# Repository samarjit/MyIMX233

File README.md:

# Let me see if I can build a linux Computer (It works now!)

I am starting to build a single board computer with freescale microprocessor iMX233 128 LQFP and 64MB DDR2 SDRAM in 66TSOP. This single board computer will be bare bones with lots of GPIO exposed.
There is no special goal for this project. I am just curious to see if it works. In future I might add an LCD. The PCB is two layered only and can be manufactured cheap.

## TODOs (done)
* Increase pad lengths of LQFP footprint. (done. Hope to mitigate the soldermask between pads issue  |<-0.06mm space-><-0.08mm web-><-0.06mm space->|  = 0.2mm) 
* Perhaps add a jumper on the 2.5v LineReg and separate out VDD_MEM to be able to test the 2.5v is not 0 due to loading. (skipped)
* 88 USB_ID SSP1_DETECT ? Should I use this to CD of SD card connector or micro USB ID pin?  In my circuit it is pulled low via LED. Tux,calculator does the same too.
* Add option to boot resistors LCD_RS and LCD_00..LCD_05 (done)
* 14 LCD_RS ? High for register boot mode. Or low with 47k resistor for OTP boot mode. Olimex is confusing OTP is set MMBR and LCD_RS is high. (done)
* Schottkey Diode D1 VDD4P2 direction. Its strange in ref diagram vs 5v wall. VDD4P2 -|>||- VDDBATT. (done Optional. Not populated in running board)
* Series resistor 1E for preventing oscillations (done 3 series resistor added, usb, batt, 4p2)
/in old circuit Test by removing Diode, and LED_RS to gnd via resistor.
* RESET circuit? Make sure not to get into USB recovery mode. add zener 1.0v so that it never reached 3.3v or just remove reset circuit altogether.
* Configure to get rid of batteries as per rev-c circuit. Add 1k resistors in DCDC_BATT and BATT and some caps to GND.
* Need to convert the SD card connector to a cheaper version available on ebay or alibaba. (done part-ATTEND 112J-TDAR-R01)
I got the files from https://forum.kicad.info/t/microsd-component-footprint-help/3095/5 and placed in parts/ folder. 
It would be awesome if I can find some 3D model of it. If someone finds it please create an issue. (Yes found)
* Make DDR RAM pin pads longer (new)
* Make alternate USB plug preferably through hole or longer pads in micro USB. (new)
* Make micro-SD pads larger and longer and add a few decoupling capacitors.(new)
* Make more rooms for the inductor as most inductors are really big 8mm long plus place for hand soldering.(new)

## TODOs (ignored)
* POWER off circuit? 
* Is Micro SD pullups on all pins necessary? SSP1_DETECT used? (done added them in the bottom side. Data3/CS pulled low)
* Added 120R between CLK nCLK.

### Length Tuning
* D0..D7 LDQS LDM - 39.7mm tuning (real 40.2mm)
* CLK nCLK - real 32.2/32.6mm
* D8..D15 UDQS UDM - 25.5mm tuning (real 26.0mm)
* Address: 32.35mm ~ 25mm
* CKE- 20.2mm
* SD: 24.8mm tuning (real 25.3mm)

## Installation steps
Cloning this repository should work.
It does use opendous
conn_fci from https://github.com/cpavlina/kicad-pcblib.git, https://github.com/cpavlina/kicad-schlib.git
Copy kicad-pcblib\conn-fci.pretty to  KiCad\share\kicad\modules\conn-fci.pretty
Add kicad-schlib-master\library\conn-fci.lib  to SchematicEditor -> ComponentLibraries
Add opendous to component libraries too.

## Drivers for this project.
* Until recently I didn't know of a decent opensource software for PCB designing or circuit designing which can be used to design complicated circuits involving microprocessor.
I recently discovered KiCAD which is opensource pcb designing software and people have done microprocessor design with it eg. OLinuXino. I am trying to learn PCB designing using KiCAD now.
* Second driver was Clementine Core project which I saw in circuitmaker website. This schematic looked so simple and pcb was on 2 layer design, which changed my thought process altogether that linux running board designs may be something I can try.
* Third driver was LibreCalc which almost proved that KiCAD can be used to design IMX233 based board. I hope to learn from their mistakes, but a newbee like me can uncover a whole lot of new mystries.

So I have put together a mashup of schematic design of IMX233 and 64MB RAM from freescale reference design and other sources. 

**Freescale microprocessor:**
* MCIMX233CAG4C

**DDR RAM - I think all these below RAM chips are compatible.**
* AS4C32M16MD1-5TCN
* HY5DU121622D(L)T(P)-J
* MT46V32M16P-5B:J (This is the only one I can source, so I am using this)

This project is a work in progress and there is no gurantee that I will ever be able to complete it :).

But if you want to try building same stuff as I am building. Go ahead and fork it.
Download KiCad. I am using nightly version of it, because it does not require you to export the netlist and import it again in pcb editor. Make the workflow really easy.
I can see one bug in KiCAD, which is after modifying the footprint by adding a step file. It looses the saved settings. 

Once you have installed KiCAD, open **MyIMX233.pro** file. 

[MyIMX233.sch](MyIMX233.sch) - Schematic file.

[MyIMX233.kicad_pcb](MyIMX233.kicad_pcb) - PCB

[ReferenceSch](ReferenceSch) - contains reference materials. I uploaded all of them for providing content incase someone wants to understand the design.

## Progress: 

### Oct 8 It worked! You can start building one today for yourself :)
Few soldering quirks are there. USB pads are quite small to solder. Also pad to hold USB in place is also very small and bad for soldering. Even the SD card pads are also small for soldering. These were new footprints so in next version I will make longer pads for these. RAM pads can be made slightly longer for reliable soldering. 
Soldered board and powered up without SD card. Some error were coming 0x80207002. Boot loader looking for I2C and it is not initialized. Turned out to be soldering of one pin was not proper for LQFP128. Fixed this pin issue then SD card missing related errors were coming. Added SD card with bogus data 0x8020A007 - ERROR_DDI_SD_CONFIG_BLOCK_NOT_FOUND. Added SD card formatted properly but still 0x8020A007. Little bit further digging showed that SD card MBR boot is not enabled by default. We need to burn an OPT bit HW_OCOTP_ROM0::SD_MBR_BOOT to enable booting from SD card. This process is irreversible. Default boot mode is BCB. I read up again librecalc's failure blog.  It gave two perl programs to burn the SD card with u-boot in BCB mode. The 2nd perl program didn't run as it assumed smaller SD cards only. I edited the perl program to make it find proper boot signatures. Now we can see something HTLC in UART console.
That's too less info to debug further. At this point I posted in freescale community. https://community.nxp.com/message/949934. I decided to blow the MBR OTP flag using BitBurner. Then added MBR based uSD card and same u-boot. Now again it shows HTLC. Good news is that MBR booting works. But it fails very soon. Need bootlets which gives more detailed log instead of u-boot. Turned out voltages are fluctuating all 3v3, 4v2, 1v8, 1v. They were fluctuating in a cycle. I burned official Olinuxino image in SD card. That seems to have bootlets so it gave more info. After right after memory `FRAC 0x92926192` it reboots. I heated up all the pins of DDR and iMX233 with soldering iron. It goes 1 more line ahead in log `init_ddr_mt46v32m16_133Mhz` and sometimes `power 0x00820710`. I added a big capacitor in place of battery which goes the log to further and says uSD card general error ending with r14<0>HTLLLL... I tried adding a few caps on 3v3. But nothing helped. Then I tried the other jumper of battery mode. Then it started loading kernel. 

### Aug 2017
Started modifying the schematic to make battery and USB wall power optional using jumpers. Also realized boot selection can be done using resistors. Sent for fabrication of PCB to pcbpower.

### July 2017 end first soldered board
Good news is most of the components fitted. Also I got some confidence about my KiCAD skills.
Some shortcomings were observed, like the pads for soldering were two short for the fine pitched LQFP128 0.4mm pitch and solder mask dams were not created between pads which made it incredibly hard to solder. I will have to customize the LQFP128 footprint to make it suitable for hand soldering. Some 0402 caps were placed very close, I realized the courtyard verification of components is not turned on by default. I had limited success like UART was working USB was working, BitBurner was working and showing all the OPT(One Time Programmable) bits. Some gibberish was coming on UART console. I used solder paste for soldering, so I thought some shorting might be happening. Then I tried to do reflow soldering to make the solder joints liquify once and then quickly cool it using a frying pan. It actually fried my board! I also mistakenly soldered uSD card with power on! Carelessness!

* I also ordered components. I didn't realize this would be a pain. element14 is not that accessible for an individual. I ordered mostly from Shelfkey and some from KitsNSpares. I am still tensed if footprints I chose will match the actual components. Second I am very much tensed about soldering 0402 components.
* Final version of PCB sent for fab in pcbpower. 

* Added few options to use DCDC. I was not comfortable of grounding DCDC_BATT and BATT pins, so I added a few jumpers. Also added provisions to add battery. 

* Learnt basic Freecad to build the Step files of DDR SDRAM 66TSOP. Here is the project I created - [MT46V32M16P-5B-Freecad-Step](https://github.com/samarjit/MT46V32M16P-5B-Freecad-Step).

* Initial version. DDR RAM child 3D missing and SD card's 3D missing.

* Learnt Length Matching in Kicad. 

* Figured out placement of components. I am going with Clementine Core's placement which seems very good.

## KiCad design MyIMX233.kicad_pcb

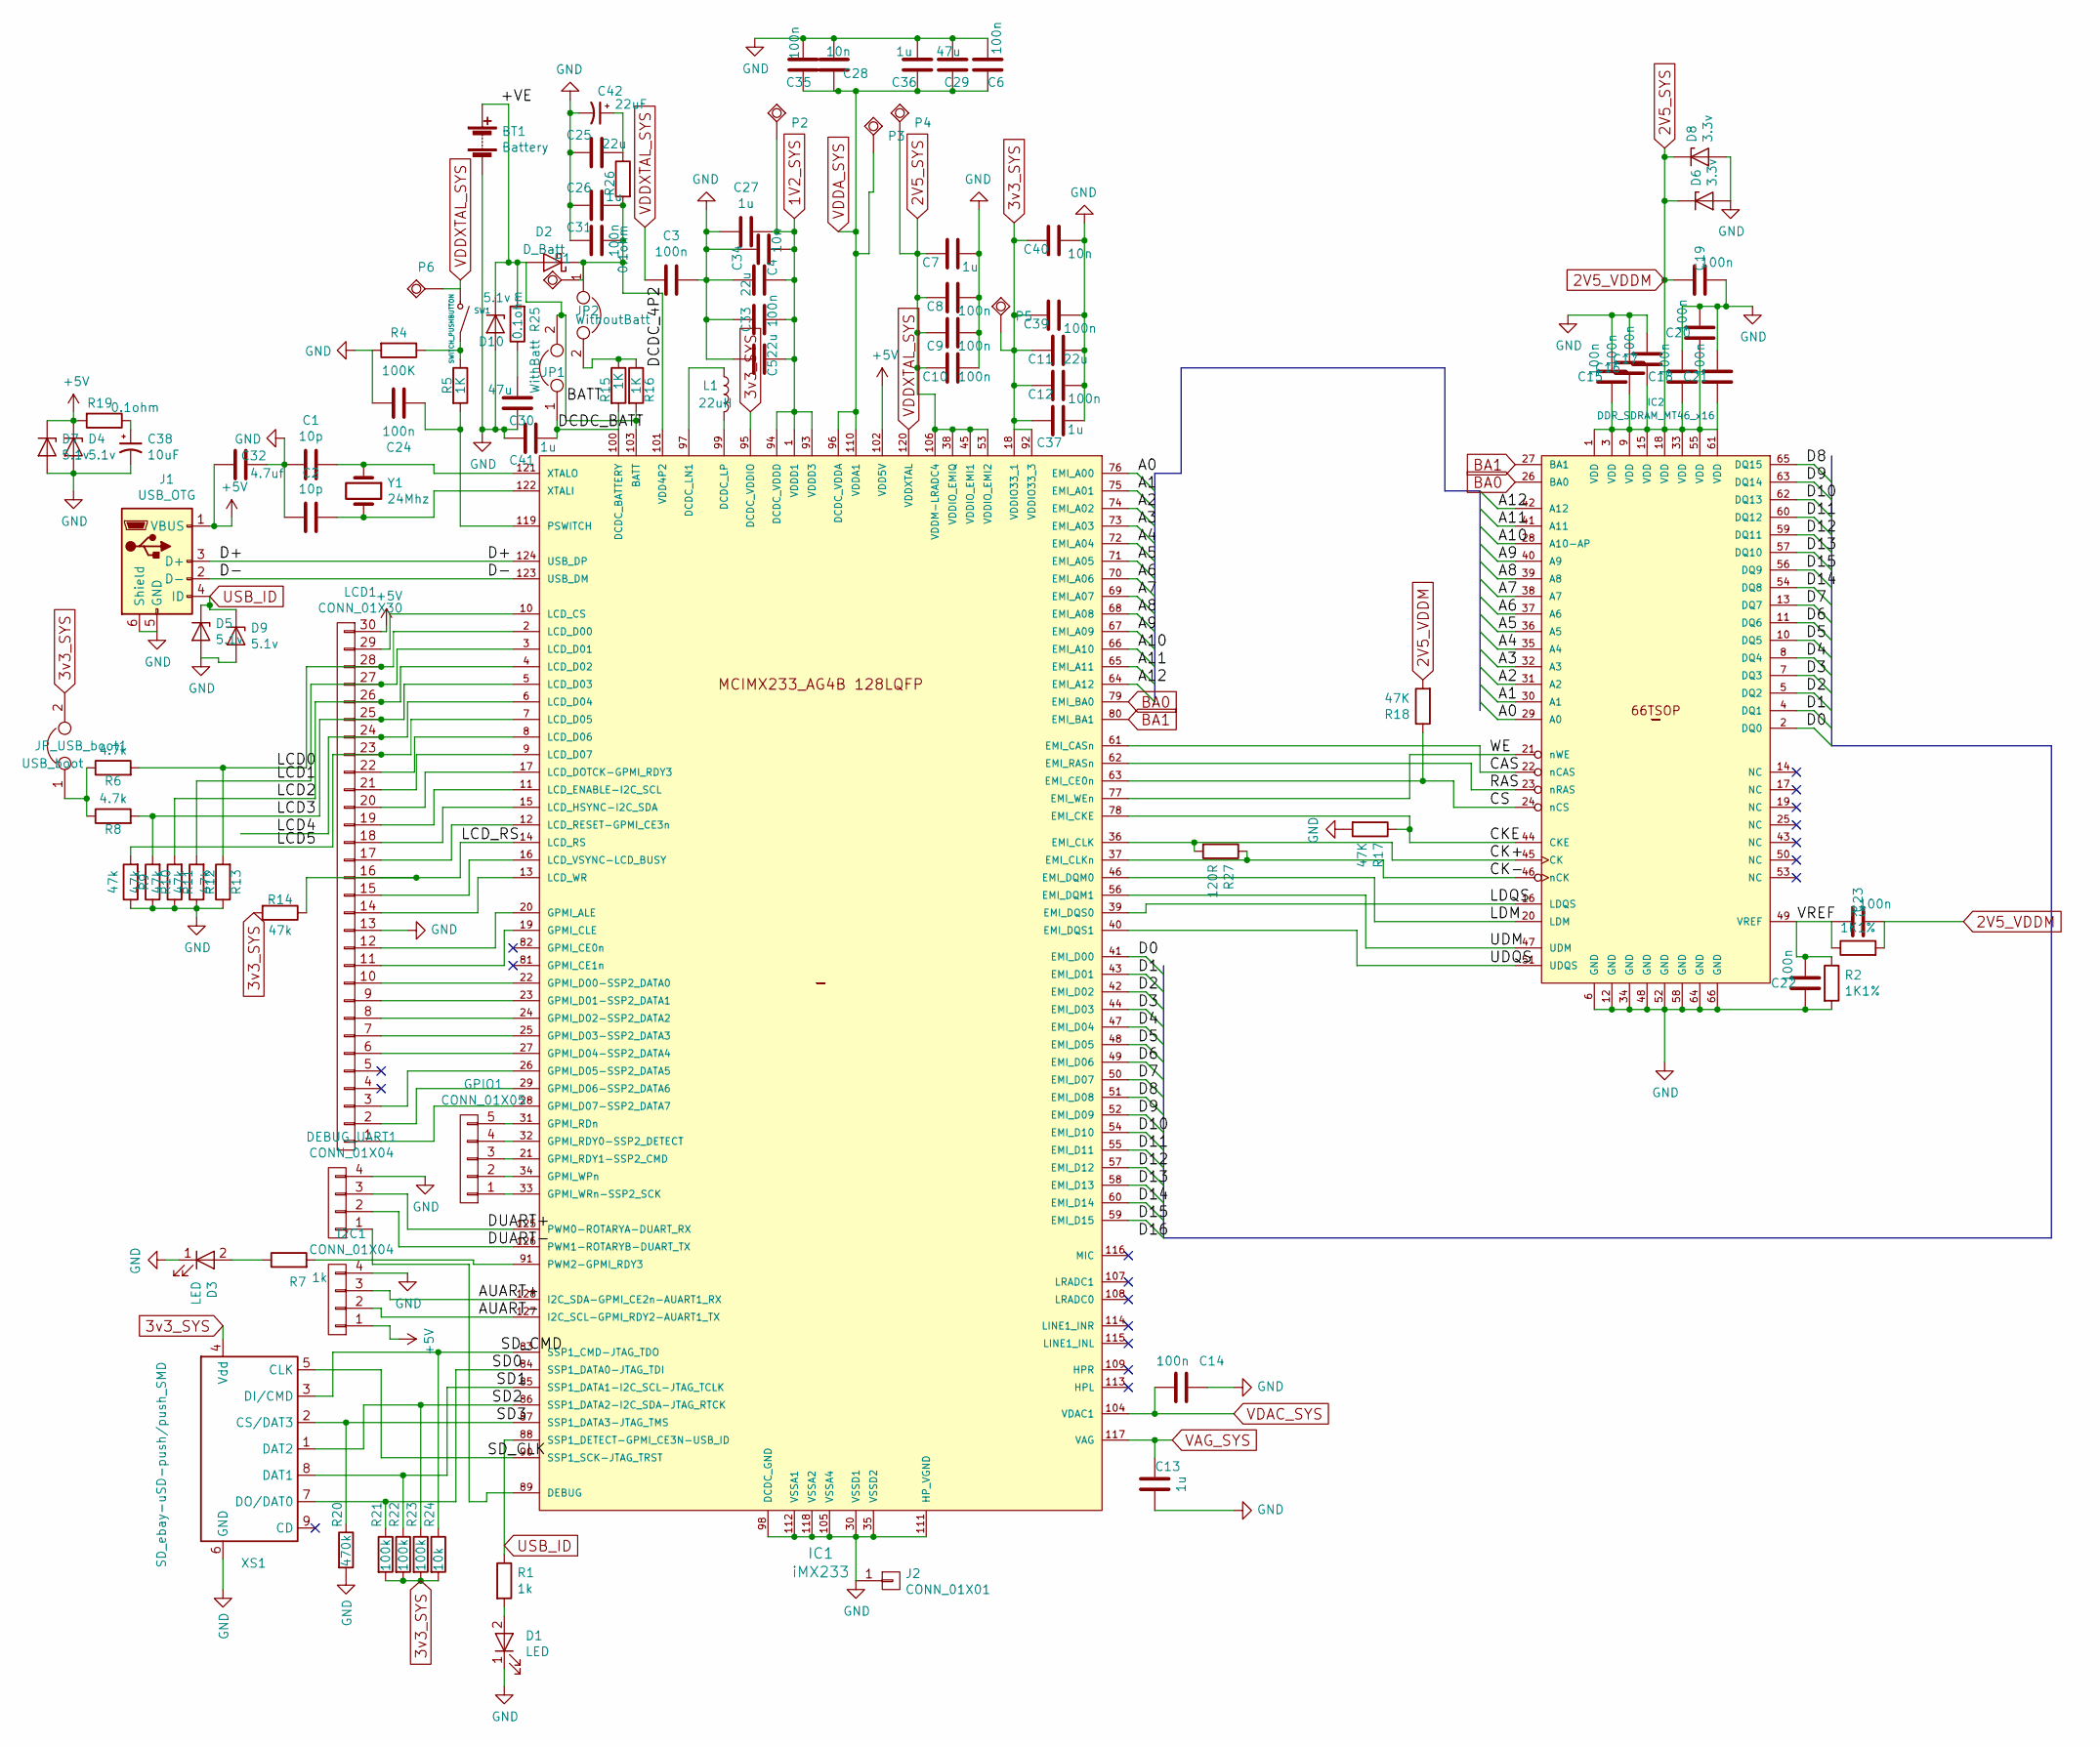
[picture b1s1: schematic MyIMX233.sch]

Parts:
BT1: Battery; JST_XH_B02B-XH-A_02x2.50mm_Straight
C1, C2: 10p; C_0402
C3, C6, C8, C9, C10, C12, C14, C15, C16, C17, C18, C19, C20, C21, C22, C23, C24, C31, C33, C35, C39: 100n; C_0402
C4, C5, C11, C25: 22u; C_0805_HandSoldering
C7: 1u; C_0805_HandSoldering
C13, C36, C37, C41: 1u; C_0603_HandSoldering
C26, C27: 1u; C_0402
C28, C34, C40: 10n; C_0402
C29, C30: 47u; C_0805_HandSoldering
C32: 4.7uf; C_0603_HandSoldering
C38: 10uF; CP_Radial_D5.0mm_P2.50mm
C42: 22uF; CP_Radial_D5.0mm_P2.50mm
D1: LED; LED_D4.0mm
D2: D_Batt; D_SOD-323_HandSoldering
D3: LED; LED_0603
D4, D5, D10: 5.1v; D_SOD-323_HandSoldering
D6: 3.3v; D_SOD-123
D7, D9: 5.1v; D_DO-35_SOD27_P7.62mm_Horizontal
D8: 3.3v; D_DO-35_SOD27_P7.62mm_Horizontal
DEBUG_UART1: CONN_01X04; Pin_Header_Straight_1x04_Pitch2.54mm
GPIO1: CONN_01X05; Pin_Header_Straight_1x05_Pitch2.54mm
I2C1: CONN_01X04; Pin_Header_Straight_1x04_Pitch2.54mm
IC1: iMX233; LQFP-128_14x14mm_Pitch0.4mm
IC2: DDR_SDRAM_MT46_x16; TSOP66_JEDEC_DDR_SDRAM
J1: USB_OTG; USB_Micro-B_MOLEX_105017-0001
J2: CONN_01X01; 1pin
JP1: WithBatt; Pin_Header_Straight_1x02_Pitch2.54mm
JP2: WithoutBatt; Pin_Header_Straight_1x02_Pitch2.54mm
JP_USB_boot1: USB_boot; Pin_Header_Straight_1x02_Pitch2.54mm
L1: 22uH; Bourns22uh6x6mm
LCD1: CONN_01X30; Pin_Header_Straight_1x30_Pitch2.54mm
P1: 4p2; GOGO_TESTPAD2
P2: 1v2; GOGO_TESTPAD2
P3: VDDA1v8; GOGO_TESTPAD2
P4: 2v5; GOGO_TESTPAD2
P5: 3v3; GOGO_TESTPAD2
P6: 1v; GOGO_TESTPAD2
R1, R7: 1k; R_0603_HandSoldering
R2, R3: 1K1%; R_0603
R4: 100K; R_0603_HandSoldering
R5: 1K; R_0603_HandSoldering
R6, R8: 4.7k; R_0603_HandSoldering
R9, R10, R11, R12, R13, R14: 47k; R_0603_HandSoldering
R15, R16: 1K; R_0603
R17, R18: 47K; R_0603
R19, R25, R26: 0.1ohm; R_0603_HandSoldering
R20: 470k; R_0603_HandSoldering
R21, R22, R23: 100k; R_0603_HandSoldering
R24: 10k; R_0603_HandSoldering
R27: 120R; R_0603
SW1: SWITCH_PUSHBUTTON; SW_PUSH_6mm
XS1: SD_ebay-uSD-push/push_SMD; uSDcard
Y1: 24Mhz; Crystal_HC49-4H_Vertical

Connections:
1V2_SYS: C4.2, C5.2, C27.2, C33.1, C34.1, IC1.1 (VDDD1), IC1.93 (VDDD3), IC1.94 (DCDC_VDDD), P2.P$1
2V5_SYS: C7.2, C8.2, C9.2, C10.2, C15.1, C16.1, C17.1, C18.1, C19.1, C20.1, C21.1, C23.2, D6.1 (K), D8.1 (K), IC1.38 (VDDIO_EMIQ), IC1.45 (VDDIO_EMI1), IC1.53 (VDDIO_EMI2), IC1.106 (VDDM-LRADC4), IC2.1 (VDD), IC2.3 (VDD), IC2.9 (VDD), IC2.15 (VDD), IC2.18 (VDD), IC2.33 (VDD), IC2.55 (VDD), IC2.61 (VDD), P4.P$1, R3.2, R18.2
3v3_SYS: C11.2, C12.2, C37.1, C39.2, C40.2, IC1.18 (VDDIO33_1), IC1.92 (VDDIO33_3), IC1.95 (DCDC_VDDIO), JP_USB_boot1.2, P5.P$1, R14.2, R21.2, R22.2, R23.2, R24.2, XS1.4 (Vdd)
+5V: C32.1, D4.1 (K), D7.1 (K), I2C1.1, IC1.102 (VDD5V), J1.1 (VBUS), LCD1.30, R19.2
/+VE: BT1.1 (+), D2.2 (A), D10.1 (K), IC1.103 (BATT), JP1.2, R16.2, R25.2
/A0: IC1.76 (EMI_A00), IC2.29 (A0)
/A1: IC1.75 (EMI_A01), IC2.30 (A1)
/A2: IC1.74 (EMI_A02), IC2.31 (A2)
/A3: IC1.73 (EMI_A03), IC2.32 (A3)
/A4: IC1.72 (EMI_A04), IC2.35 (A4)
/A5: IC1.71 (EMI_A05), IC2.36 (A5)
/A6: IC1.70 (EMI_A06), IC2.37 (A6)
/A7: IC1.69 (EMI_A07), IC2.38 (A7)
/A8: IC1.68 (EMI_A08), IC2.39 (A8)
/A9: IC1.67 (EMI_A09), IC2.40 (A9)
/A10: IC1.66 (EMI_A10), IC2.28 (A10-AP)
/A11: IC1.65 (EMI_A11), IC2.41 (A11)
/A12: IC1.64 (EMI_A12), IC2.42 (A12)
/AUART+: I2C1.3, IC1.128 (I2C_SDA-GPMI_CE2n-AUART1_RX)
/AUART-: I2C1.2, IC1.127 (I2C_SCL-GPMI_RDY2-AUART1_TX)
/CAS: IC1.61 (EMI_CASn), IC2.22 (nCAS)
/CK+: IC1.36 (EMI_CLK), IC2.45 (CK), R27.2
/CK-: IC1.37 (EMI_CLKn), IC2.46 (nCK), R27.1
/CKE: IC1.78 (EMI_CKE), IC2.44 (CKE), R17.1
/CS: IC1.63 (EMI_CE0n), IC2.24 (nCS), R18.1
/D0: IC1.41 (EMI_D00), IC2.2 (DQ0)
/D1: IC1.43 (EMI_D01), IC2.4 (DQ1)
/D2: IC1.42 (EMI_D02), IC2.5 (DQ2)
/D3: IC1.44 (EMI_D03), IC2.7 (DQ3)
/D4: IC1.47 (EMI_D04), IC2.8 (DQ4)
/D5: IC1.48 (EMI_D05), IC2.10 (DQ5)
/D6: IC1.49 (EMI_D06), IC2.11 (DQ6)
/D7: IC1.50 (EMI_D07), IC2.13 (DQ7)
/D8: IC1.51 (EMI_D08), IC2.65 (DQ15)
/D9: IC1.52 (EMI_D09), IC2.63 (DQ14)
/D10: IC1.54 (EMI_D10), IC2.62 (DQ13)
/D11: IC1.55 (EMI_D11), IC2.60 (DQ12)
/D12: IC1.57 (EMI_D12), IC2.59 (DQ11)
/D13: IC1.58 (EMI_D13), IC2.57 (DQ10)
/D14: IC1.60 (EMI_D14), IC2.54 (DQ8)
/D15: IC1.59 (EMI_D15), IC2.56 (DQ9)
/D+: IC1.124 (USB_DP), J1.3 (D+)
/D-: IC1.123 (USB_DM), J1.2 (D-)
/DCDC_4P2: C26.2, C31.1, D2.1 (K), IC1.101 (VDD4P2), JP2.1, P1.P$1, R26.2
/DCDC_BATT: C41.2, IC1.100 (DCDC_BATTERY), JP1.1, R15.2
/DUART+: DEBUG_UART1.3, IC1.125 (PWM0-ROTARYA-DUART_RX)
/DUART-: DEBUG_UART1.2, IC1.126 (PWM1-ROTARYB-DUART_TX)
/LCD0: IC1.2 (LCD_D00), LCD1.28, R6.2, R13.2
/LCD1: IC1.3 (LCD_D01), LCD1.27, R12.2
/LCD2: IC1.4 (LCD_D02), LCD1.26, R11.2
/LCD3: IC1.5 (LCD_D03), LCD1.25, R8.2, R10.2
/LCD4: IC1.6 (LCD_D04), LCD1.24
/LCD5: IC1.7 (LCD_D05), LCD1.23, R9.2
/LCD_RS: IC1.14 (LCD_RS), LCD1.16, R14.1
/LDM: IC1.46 (EMI_DQM0), IC2.20 (LDM)
/LDQS: IC1.39 (EMI_DQS0), IC2.16 (LDQS)
/RAS: IC1.62 (EMI_RASn), IC2.23 (nRAS)
/SD0: IC1.84 (SSP1_DATA0-JTAG_TDI), R21.1, XS1.7 (DO/DAT0)
/SD1: IC1.85 (SSP1_DATA1-I2C_SCL-JTAG_TCLK), R22.1, XS1.8 (DAT1)
/SD2: IC1.86 (SSP1_DATA2-I2C_SDA-JTAG_RTCK), R23.1, XS1.1 (DAT2)
/SD3: IC1.87 (SSP1_DATA3-JTAG_TMS), R20.1, XS1.2 (CS/DAT3)
/SD_CLK: IC1.90 (SSP1_SCK-JTAG_TRST), XS1.5 (CLK)
/SD_CMD: IC1.83 (SSP1_CMD-JTAG_TDO), R24.1, XS1.3 (DI/CMD)
/UDM: IC1.56 (EMI_DQM1), IC2.47 (UDM)
/UDQS: IC1.40 (EMI_DQS1), IC2.51 (UDQS)
/VREF: C22.2, C23.1, IC2.49 (VREF), R2.1, R3.1
/WE: IC1.77 (EMI_WEn), IC2.21 (nWE)
BA0: IC1.79 (EMI_BA0), IC2.26 (BA0)
BA1: IC1.80 (EMI_BA1), IC2.27 (BA1)
GND: BT1.2 (-), C1.1, C2.1, C3.2, C4.1, C5.1, C6.1, C7.1, C8.1, C9.1, C10.1, C11.1, C12.1, C13.2, C14.1, C15.2, C16.2, C17.2, C18.2, C19.2, C20.2, C21.2, C22.1, C24.1, C25.1, C26.1, C27.1, C28.1, C29.1, C30.2, C31.2, C32.2, C33.2, C34.2, C35.1, C36.1, C37.2, C38.2, C39.1, C40.1, C41.1, C42.2, D1.1 (K), D3.1 (K), D4.2 (A), D5.2 (A), D6.2 (A), D7.2 (A), D8.2 (A), D9.2 (A), D10.2 (A), DEBUG_UART1.4, I2C1.4, IC1.30 (VSSD1), IC1.35 (VSSD2), IC1.98 (DCDC_GND), IC1.105 (VSSA4), IC1.111 (HP_VGND), IC1.112 (VSSA1), IC1.118 (VSSA2), IC2.6 (GND), IC2.12 (GND), IC2.34 (GND), IC2.48 (GND), IC2.52 (GND), IC2.58 (GND), IC2.64 (GND), IC2.66 (GND), J1.5 (GND), J1.6 (Shield), J2.1, LCD1.13, R2.2, R4.2, R9.1, R10.1, R11.1, R12.1, R13.1, R17.2, R20.2, XS1.6 (GND)
unnamed: C1.2, IC1.121 (XTALO), Y1.1
unnamed: C2.2, IC1.122 (XTALI), Y1.2
unnamed: C24.2, IC1.119 (PSWITCH), R5.2
unnamed: C25.2, C42.1, R26.1
unnamed: C30.1, R25.1
unnamed: C38.1, R19.1
unnamed: D1.2 (A), R1.2
unnamed: D3.2 (A), R7.1
unnamed: DEBUG_UART1.1, IC1.89 (DEBUG)
unnamed: GPIO1.1, IC1.33 (GPMI_WRn-SSP2_SCK)
unnamed: GPIO1.2, IC1.34 (GPMI_WPn)
unnamed: GPIO1.3, IC1.21 (GPMI_RDY1-SSP2_CMD)
unnamed: GPIO1.4, IC1.32 (GPMI_RDY0-SSP2_DETECT)
unnamed: GPIO1.5, IC1.31 (GPMI_RDn)
unnamed: IC1.8 (LCD_D06), LCD1.22
unnamed: IC1.9 (LCD_D07), LCD1.21
unnamed: IC1.10 (LCD_CS), LCD1.29
unnamed: IC1.11 (LCD_ENABLE-I2C_SCL), LCD1.19
unnamed: IC1.12 (LCD_RESET-GPMI_CE3n), LCD1.17
unnamed: IC1.13 (LCD_WR), LCD1.14
unnamed: IC1.15 (LCD_HSYNC-I2C_SDA), LCD1.18
unnamed: IC1.16 (LCD_VSYNC-LCD_BUSY), LCD1.15
unnamed: IC1.17 (LCD_DOTCK-GPMI_RDY3), LCD1.20
unnamed: IC1.19 (GPMI_CLE), LCD1.11
unnamed: IC1.20 (GPMI_ALE), LCD1.12
unnamed: IC1.22 (GPMI_D00-SSP2_DATA0), LCD1.10
unnamed: IC1.23 (GPMI_D01-SSP2_DATA1), LCD1.9
unnamed: IC1.24 (GPMI_D02-SSP2_DATA2), LCD1.8
unnamed: IC1.25 (GPMI_D03-SSP2_DATA3), LCD1.7
unnamed: IC1.26 (GPMI_D05-SSP2_DATA5), LCD1.3
unnamed: IC1.27 (GPMI_D04-SSP2_DATA4), LCD1.6
unnamed: IC1.28 (GPMI_D07-SSP2_DATA7), LCD1.1
unnamed: IC1.29 (GPMI_D06-SSP2_DATA6), LCD1.2
unnamed: IC1.91 (PWM2-GPMI_RDY3), R7.2
unnamed: IC1.97 (DCDC_LN1), L1.1
unnamed: IC1.99 (DCDC_LP), L1.2
unnamed: JP2.2, R15.1, R16.1
unnamed: JP_USB_boot1.1, R6.1, R8.1
unnamed: R4.1, R5.1, SW1.2 (B)
USB_ID: D5.1 (K), D9.1 (K), IC1.88 (SSP1_DETECT-GPMI_CE3N-USB_ID), J1.4 (ID), R1.1
VAG_SYS: C13.1, IC1.117 (VAG)
VDAC_SYS: C14.2, IC1.104 (VDAC1)
VDDA_SYS: C6.2, C28.2, C29.2, C35.2, C36.2, IC1.96 (DCDC_VDDA), IC1.110 (VDDA1), P3.P$1
VDDXTAL_SYS: C3.1, IC1.120 (VDDXTAL), P6.P$1, SW1.1 (A)

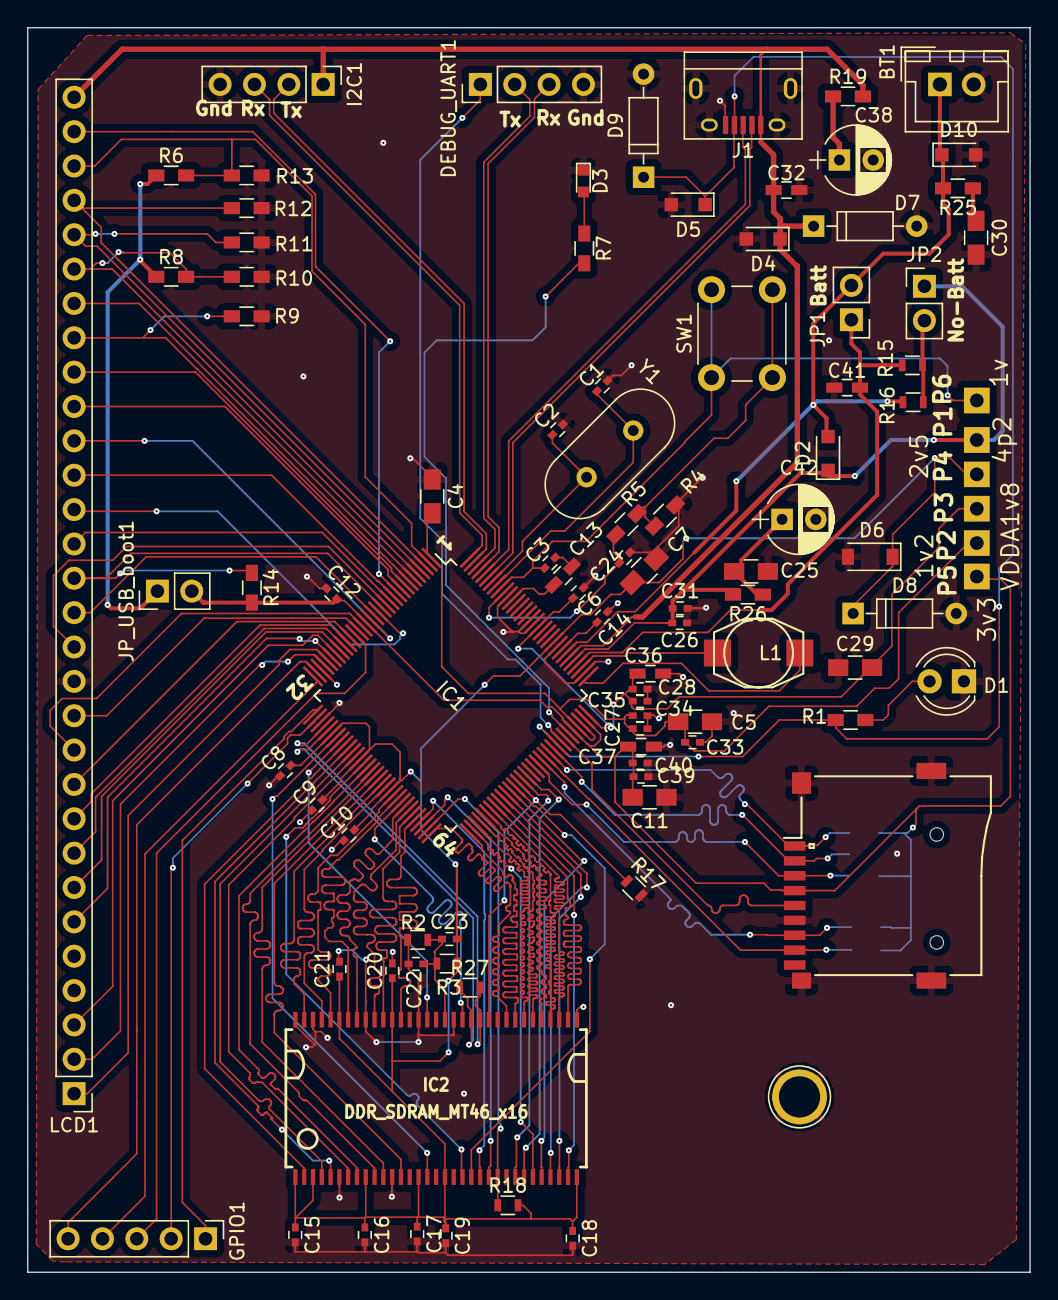
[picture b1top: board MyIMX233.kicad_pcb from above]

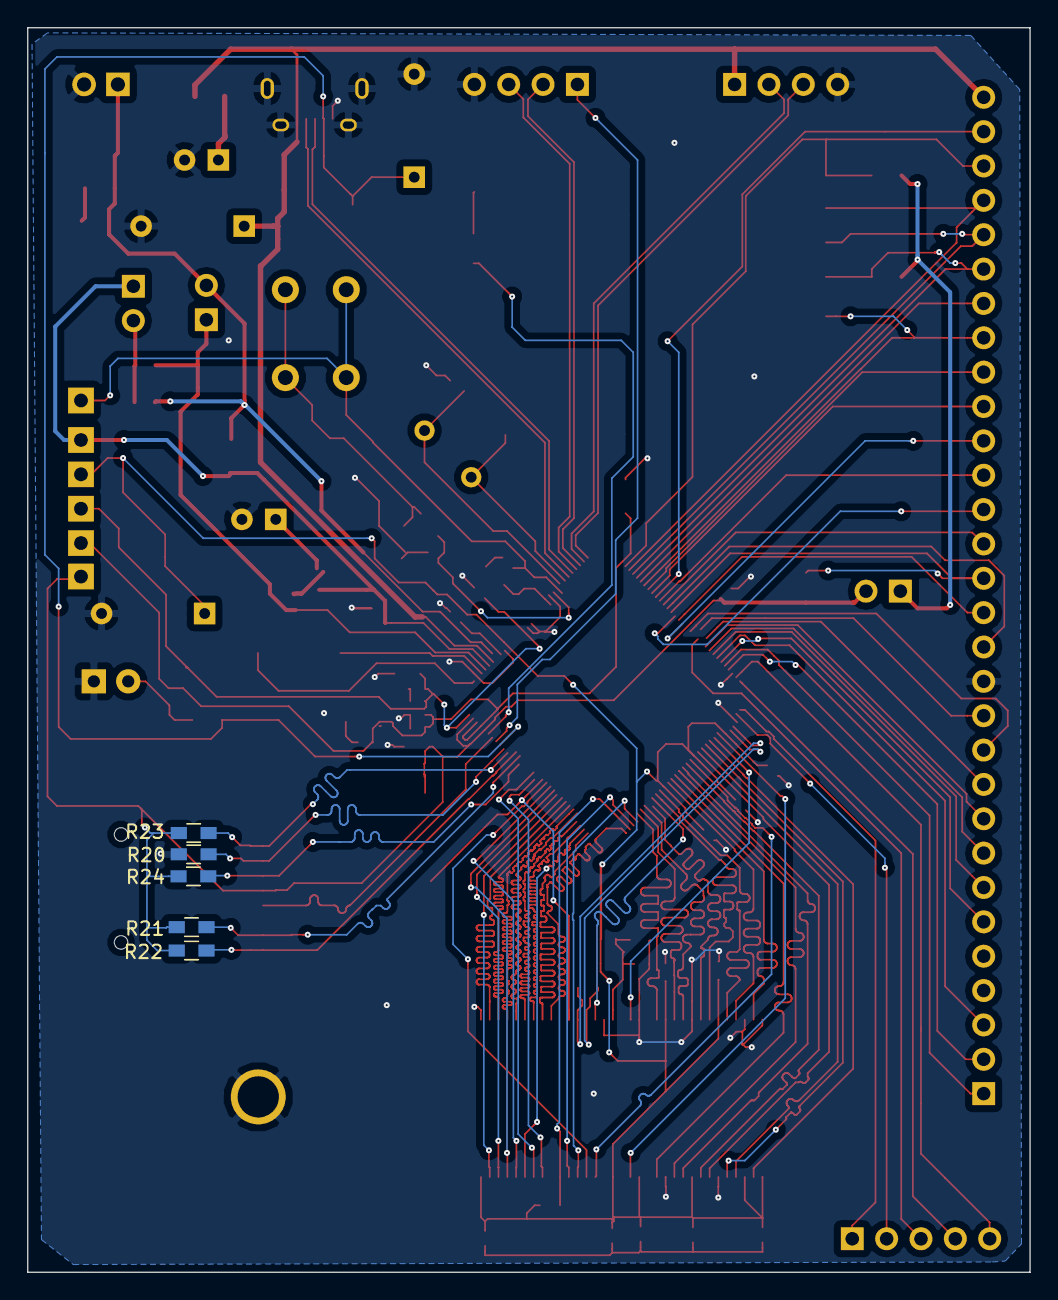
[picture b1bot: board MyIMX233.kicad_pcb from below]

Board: 2 copper layers, 74.1 x 92.0 mm, 101 parts (5 on the bottom side), 114 nets.

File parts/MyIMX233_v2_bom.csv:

"Id";"Designator";"Package";"Quantity";"Designation";"Supplier and ref";
1;"J2";"1pin";1;"CONN_01X01";;;
2;"C42";"CP_Radial_D5.0mm_P2.50mm";1;"22uF";;;
3;"R27";"R_0603";1;"120R";;;
4;"R25,R26,R19";"R_0603_HandSoldering";3;"0.1ohm";;;
5;"R20";"R_0603_HandSoldering";1;"470k";;;
6;"R21,R23,R22";"R_0603_HandSoldering";3;"100k";;;
7;"R24";"R_0603_HandSoldering";1;"10k";;;
8;"D10,D4,D5";"D_SOD-323_HandSoldering";3;"5.1v";;;
9;"C41,C37,C36,C13";"C_0603_HandSoldering";4;"1u";;;
10;"D7,D9";"D_DO-35_SOD27_P7.62mm_Horizontal";2;"5.1v";;;
11;"D8";"D_DO-35_SOD27_P7.62mm_Horizontal";1;"3.3v";;;
12;"C38";"CP_Radial_D5.0mm_P2.50mm";1;"10uF";;;
13;"D6";"D_SOD-123";1;"3.3v";;;
14;"R17,R18";"R_0603";2;"47K";;;
15;"XS1";"uSDcard";1;"SD_ebay-uSD-push/push_SMD";;;
16;"IC1";"LQFP-128_14x14mm_Pitch0.4mm";1;"iMX233";;;
17;"Y1";"Crystal_HC49-4H_Vertical";1;"24Mhz";;;
18;"JP_USB_boot1";"Pin_Header_Straight_1x02_Pitch2.54mm";1;"USB_boot";;;
19;"JP1";"Pin_Header_Straight_1x02_Pitch2.54mm";1;"WithBatt";;;
20;"R15,R16";"R_0603";2;"1K";;;
21;"J1";"USB_Micro-B_MOLEX_105017-0001";1;"USB_OTG";;;
22;"R6,R8";"R_0603_HandSoldering";2;"4.7k";;;
23;"R14,R13,R9,R12,R10,R11";"R_0603_HandSoldering";6;"47k";;;
24;"P6";"GOGO_TESTPAD2";1;"1v";;;
25;"D3";"LED_0603";1;"LED";;;
26;"R7,R1";"R_0603_HandSoldering";2;"1k";;;
27;"P1";"GOGO_TESTPAD2";1;"4p2";;;
28;"P2";"GOGO_TESTPAD2";1;"1v2";;;
29;"P4";"GOGO_TESTPAD2";1;"2v5";;;
30;"P5";"GOGO_TESTPAD2";1;"3v3";;;
31;"P3";"GOGO_TESTPAD2";1;"VDDA1v8";;;
32;"C12,C39,C24,C33,C35,C31,C8,C20,C19,C18,C17,C16,C23,C14,C10,C9,C6,C3,C15,C21,C22";"C_0402";21;"100n";;;
33;"C40,C34,C28";"C_0402";3;"10n";;;
34;"R3,R2";"R_0603";2;"1K1%";;;
35;"C32";"C_0603_HandSoldering";1;"4.7uf";;;
36;"C30,C29";"C_0805_HandSoldering";2;"47u";;;
37;"BT1";"JST_XH_B02B-XH-A_02x2.50mm_Straight";1;"Battery";;;
38;"D2";"D_SOD-323_HandSoldering";1;"D_Batt";;;
39;"R5";"R_0603_HandSoldering";1;"1K";;;
40;"R4";"R_0603_HandSoldering";1;"100K";;;
41;"IC2";"TSOP66_JEDEC_DDR_SDRAM";1;"DDR_SDRAM_MT46_x16";;;
42;"DEBUG_UART1,I2C1";"Pin_Header_Straight_1x04_Pitch2.54mm";2;"CONN_01X04";;;
43;"JP2";"Pin_Header_Straight_1x02_Pitch2.54mm";1;"WithoutBatt";;;
44;"L1";"Bourns22uh6x6mm";1;"22uH";;;
45;"C26,C27";"C_0402";2;"1u";;;
46;"C25,C11,C5,C4";"C_0805_HandSoldering";4;"22u";;;
47;"LCD1";"Pin_Header_Straight_1x30_Pitch2.54mm";1;"CONN_01X30";;;
48;"GPIO1";"Pin_Header_Straight_1x05_Pitch2.54mm";1;"CONN_01X05";;;
49;"C1,C2";"C_0402";2;"10p";;;
50;"SW1";"SW_PUSH_6mm";1;"SWITCH_PUSHBUTTON";;;
51;"C7";"C_0805_HandSoldering";1;"1u";;;
52;"D1";"LED_D4.0mm";1;"LED";;;

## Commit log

2017-05-01 first schematic
2017-05-01 footprint mapped
2017-05-07 pcb without length matching and plot
2017-05-08 pcb without length matching added
2017-05-08 refs committed
2017-05-09 lane 1 length matched 42.4
2017-05-10 refs added plus tuned lengths of d8..15 and addr
2017-05-13 length matched
2017-05-19 updated pcb export with 3d step files plus my new DDR step and FreeCAD proj
2017-06-01 before dcdc
2017-06-07 updated with step files new battery and inductor diag
2017-06-07 updated cap comparision
2017-06-10 pcb-1.0
2017-06-10 pcb gerber sent
2017-06-10 readme updated
2017-06-10 verification file added
2017-06-16 updated via size
2017-08-10 2nd version
2017-08-10 updated README and added uSD mod and lib which might work without 3D
2017-08-11 readme updated with todo points
2017-08-15 new uSD card connector added
2017-08-15 usb footprint updated
2017-08-15 added boot resistors and 2.5v_VDDM is separated for ram, new battery connections with resistors for non battery mode
2017-08-15 resistors placement
2017-08-18 boot resistors added
2017-08-20 re routed because of pad length extention to 2mm. Generated gerver files too
2017-08-20 updated SD card line tuning
2017-08-20 updated readme added 3d step model for SD card
2017-08-20 some more export schematic and pcb images added
2017-08-21 added electrolytic caps and fixed a bug in RAM CS and CE resistors
2017-08-25 squashed 5 commits
2017-08-27 added SD data resistors, clk nCLK resistor, series resistor to stop oscillation
2017-08-27 added optional 22uf electrolyte cap in 4p2
2017-08-27 mounting hole added once for all time in schematic
2017-08-29 kicad removed unconnected wire and added bill of materials plus some images in kitsnspares
2017-08-29 clk nclk termination resistor position fixed and due to which some more length tuning of udq udm
2017-08-29 gerber created again
2017-10-08 first time working board
2017-10-08 it works now
